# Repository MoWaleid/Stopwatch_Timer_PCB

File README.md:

# Programmable Logic Timer & Stopwatch (Digital Logic Design)

## Project Overview
A hardware-defined digital timing system engineered using **discrete logic ICs**. This project operates without a microcontroller, utilizing synchronous counters and combinational logic to provide high-precision **Stopwatch (Count-Up)** and **Timer (Countdown)** functionality. The system automates a **220V AC load** via a relay interface upon reaching a user-defined time target.

---

## Core Features
* **Dual Mode:** Stopwatch (00:00 to Target) and Timer (Start Time to 00:00).
* **MM:SS Display:** 4-digit 7-segment output.
* **Hardware Control:** Dedicated tactile buttons for **Set**, **Start/Pause**, and **Reset**.
* **Industrial Interfacing:** Relay module for 220V appliance automation.

---

## Technical Architecture
* **Time Base:** 1Hz pulse generation via a precision **555 Timer** circuit.
* **Logic Core:** Cascaded **74LS192** BCD up/down counters managed by logic gates for state transitions.
* **Display Driver:** **74LS47** BCD-to-7-segment decoders with multiplexing logic.
* **Trigger Logic:** Gate-level detection (AND/NOR) to activate the relay at the target time or zero.
* **Power Stage:** 5V DC logic isolated from the 220V AC output using a relay driver.

---

## Design & Implementation
1.  **Simulation:** Full functional validation in **Proteus** to verify synchronous timing and gate-level logic.
2.  **Schematic Capture:** Professional circuit design in **KiCad**.
3.  **PCB Layout:** Designed a production-ready PCB in **KiCad**, implementing specific trace widths for high-voltage safety and signal integrity.

---

## Components List
* **Counters:** 74LS192 BCD Counters.
* **Decoders:** 74LS47 BCD-to-7-Segment.
* **Logic Gates:** 74LS08 (AND), 74LS32 (OR), 74LS04 (NOT).
* **Timer:** NE555.
* **Output:** 5V Relay, LED.

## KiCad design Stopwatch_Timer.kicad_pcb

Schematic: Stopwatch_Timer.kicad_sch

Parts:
AFF1, AFF2, AFF3, AFF4: LTS-6960HR; 7SegmentLED_LTS6760_LTS6780
C1: 10u; C_Radial_D5.0mm_H11.0mm_P2.00mm
C2: 10n; C_Disc_D5.0mm_W2.5mm_P5.00mm
J3: Conn_01x06_Socket; PinSocket_1x06_P2.54mm_Vertical
MT1: 74LS192; DIP-16_W7.62mm_Socket
MU1: 74LS192; DIP-16_W7.62mm_Socket
R1: 1k; R_Axial_DIN0207_L6.3mm_D2.5mm_P7.62mm_Horizontal
R1_Timer1, R2_Timer1: 22k; R_Axial_DIN0207_L6.3mm_D2.5mm_P7.62mm_Horizontal
R3, R32, R33, R34, R35, R36, R37, R38, R40, R41, R42, R43, R44, R45, R46, R47: 330; R_Axial_DIN0207_L6.3mm_D2.5mm_P10.16mm_Horizontal
R3_Timer1, R4_Timer1, R5_Timer1, R6_Timer1, R50: 10k; R_Axial_DIN0207_L6.3mm_D2.5mm_P7.62mm_Horizontal
R4, R5, R6, R7, R8, R9, R10, R11, R12, R13, R14, R15, R16, R17, R18, R19, R20, R21, R22, R23, R24, R25, R26, R27, R28, R29, R30, R31, R39, R49: 330; R_Axial_DIN0207_L6.3mm_D2.5mm_P7.62mm_Horizontal
R_Mode1: 330; R_Axial_DIN0207_L6.3mm_D2.5mm_P7.62mm_Horizontal
S3, S4, S5: BUTT-2; SW_BUTT-2; PARTREV N/A
ST1: 74LS192; DIP-16_W7.62mm_Socket
SU1: 74LS192; DIP-16_W7.62mm_Socket
SW1, SW3: SW_DIP_x08; SW_DIP_SPSTx08_Slide_6.7x21.88mm_W7.62mm_P2.54mm_LowProfile
SW2: SW_DIP_x04; SW_DIP_SPSTx04_Slide_6.7x11.72mm_W7.62mm_P2.54mm_LowProfile
U1: NE555P; DIP-8_W7.62mm_Socket
U4, U6, U7, U9: 74LS47; DIP-16_W7.62mm_Socket
U10: 74LS157; DIP-16_W7.62mm_Socket
U11, U13: SN74HC04N; DIP-14_W7.62mm_Socket
U12, U21: CD4075BE; DIP-14_W7.62mm_Socket; DigiKey_Part_Number 296-2065-5-ND
U18, U20, U23: SN74HC32N; DIP-14_W7.62mm_Socket
U19, U24: SN74HC08N; DIP-14_W7.62mm_Socket
U22: CD4023BE; DIP-14_W7.62mm_Socket

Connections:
+5V: AFF1.3 (C.A.), AFF1.5 (DP), AFF1.8 (C.A.), AFF2.3 (C.A.), AFF2.5 (DP), AFF2.8 (C.A.), AFF3.3 (C.A.), AFF3.5 (DP), AFF3.8 (C.A.), AFF4.3 (C.A.), AFF4.5 (DP), AFF4.8 (C.A.), J3.1, J3.4, MT1.16 (VCC), MU1.16 (VCC), R1.2, R50.1, S4.1, S5.2, ST1.16 (VCC), SU1.16 (VCC), SW1.1, SW1.2, SW1.3, SW1.4, SW1.5, SW1.6, SW1.7, SW1.8, SW2.1, SW3.1, SW3.2, SW3.3, SW3.4, SW3.5, SW3.6, SW3.7, SW3.8, U1.4 (~RST), U1.8 (VCC), U4.3 (LT), U4.4 (BI), U4.5 (RBI), U4.16 (VCC), U6.3 (LT), U6.4 (BI), U6.5 (RBI), U6.16 (VCC), U7.3 (LT), U7.4 (BI), U7.5 (RBI), U7.16 (VCC), U9.3 (LT), U9.4 (BI), U9.5 (RBI), U9.16 (VCC), U10.3 (I1a), U10.10 (I1c), U10.16 (VCC), U11.14 (VCC), U12.14 (VDD), U13.14 (VCC), U18.14 (VCC), U19.14 (VCC), U20.14 (VCC), U21.14 (VDD), U22.8 (C), U22.14 (VDD), U24.14 (VCC)
GND: C1.2, C2.2, J3.2, J3.6, MT1.8 (GND), MU1.8 (GND), R3.2, R32.2, R33.2, R34.2, R35.2, R36.2, R37.2, R38.2, R40.2, R41.2, R42.2, R43.2, R44.2, R45.2, R46.2, R47.2, R49.2, R_Mode1.2, S3.1, ST1.8 (GND), SU1.8 (GND), U1.1 (GND), U4.8 (GND), U6.8 (GND), U7.8 (GND), U9.8 (GND), U10.6 (I1b), U10.8 (GND), U10.13 (I1d), U10.15 (E), U11.7 (GND), U12.7 (VSS), U13.7 (GND), U18.7 (GND), U19.7 (GND), U20.7 (GND), U21.7 (VSS), U22.7 (VSS), U23.7 (GND), U24.7 (GND), U24.12 (4A), U24.13 (4B)
unnamed: AFF1.7 (a), R4.2
unnamed: AFF1.6 (b), R5.2
unnamed: AFF1.4 (c), R6.2
unnamed: AFF1.2 (d), R7.2
unnamed: AFF1.1 (e), R8.2
unnamed: AFF1.9 (f), R9.2
unnamed: AFF1.10 (g), R10.2
unnamed: AFF2.7 (a), R11.2
unnamed: AFF2.6 (b), R12.2
unnamed: AFF2.4 (c), R13.2
unnamed: AFF2.2 (d), R14.2
unnamed: AFF2.1 (e), R15.2
unnamed: AFF2.9 (f), R16.2
unnamed: AFF2.10 (g), R17.2
unnamed: AFF3.7 (a), R18.2
unnamed: AFF3.6 (b), R19.2
unnamed: AFF3.4 (c), R20.2
unnamed: AFF3.2 (d), R21.2
unnamed: AFF3.1 (e), R22.2
unnamed: AFF3.9 (f), R23.2
unnamed: AFF3.10 (g), R24.2
unnamed: AFF4.7 (a), R25.2
unnamed: AFF4.6 (b), R26.2
unnamed: AFF4.4 (c), R27.2
unnamed: AFF4.2 (d), R28.2
unnamed: AFF4.1 (e), R29.2
unnamed: AFF4.9 (f), R30.2
unnamed: AFF4.10 (g), R31.2
unnamed: J3.5, U13.13 (6A), U18.8 (3Y)
unnamed: MT1.15 (A), R43.1, SW3.13
unnamed: MT1.1 (B), R42.1, SW3.14
unnamed: MT1.10 (C), R41.1, SW3.15
unnamed: MT1.14 (CLR), MU1.14 (CLR), SU1.14 (CLR), U20.8 (3Y), U23.2 (1B)
unnamed: MT1.9 (D), R40.1, SW3.16
unnamed: MT1.4 (DOWN), MU1.13 (~BO)
unnamed: MT1.3 (QA), U6.7 (A), U21.1 (A)
unnamed: MT1.2 (QB), U6.1 (B), U21.2 (B)
unnamed: MT1.6 (QC), U6.2 (C), U21.8 (C)
unnamed: MT1.7 (QD), U6.6 (D), U21.3 (D)
unnamed: MT1.5 (UP), MU1.12 (~CO)
unnamed: MT1.11 (~LOAD), MU1.11 (~LOAD), R50.2, S3.2, SU1.11 (~LOAD), U19.1 (1A), U24.1 (1A)
unnamed: MU1.15 (A), R47.1, SW3.9
unnamed: MU1.1 (B), R46.1, SW3.10
unnamed: MU1.10 (C), R45.1, SW3.11
unnamed: MU1.9 (D), R44.1, SW3.12
unnamed: MU1.4 (DOWN), ST1.13 (~BO)
unnamed: MU1.3 (QA), U4.7 (A), U21.4 (E)
unnamed: MU1.2 (QB), U4.1 (B), U21.5 (F)
unnamed: MU1.6 (QC), U4.2 (C), U21.13 (G)
unnamed: MU1.7 (QD), U4.6 (D), U21.12 (H)
unnamed: MU1.5 (UP), U11.4 (2Y)
unnamed: R1_Timer1.2, R2_Timer1.1
unnamed: R2_Timer1.2, R3_Timer1.1
unnamed: R3_Timer1.2, R4_Timer1.1
unnamed: R4_Timer1.2, R5_Timer1.1
unnamed: R5_Timer1.2, R6_Timer1.1
unnamed: ST1.15 (A), U10.4 (Za)
unnamed: ST1.1 (B), U10.7 (Zb)
unnamed: ST1.10 (C), U10.9 (Zc)
unnamed: ST1.14 (CLR), U23.3 (1Y)
unnamed: ST1.9 (D), U10.12 (Zd)
unnamed: ST1.4 (DOWN), SU1.13 (~BO)
unnamed: ST1.3 (QA), U7.7 (A), U21.11 (I), U22.1 (A)
unnamed: ST1.2 (QB), U7.1 (B), U12.1 (A), U24.9 (3A)
unnamed: ST1.6 (QC), U7.2 (C), U12.2 (B), U24.10 (3B)
unnamed: ST1.7 (QD), U7.6 (D), U12.8 (C), U22.2 (B)
unnamed: ST1.5 (UP), SU1.12 (~CO)
unnamed: ST1.11 (~LOAD), U24.3 (1Y)
unnamed: R38.1, SU1.15 (A), SW1.9
unnamed: R37.1, SU1.1 (B), SW1.10
unnamed: R36.1, SU1.10 (C), SW1.11
unnamed: R35.1, SU1.9 (D), SW1.12
unnamed: SU1.4 (DOWN), U20.6 (2Y)
unnamed: SU1.3 (QA), U9.7 (A), U12.3 (D)
unnamed: SU1.2 (QB), U9.1 (B), U12.4 (E)
unnamed: SU1.6 (QC), U9.2 (C), U12.5 (F)
unnamed: SU1.7 (QD), U9.6 (D), U12.13 (G)
unnamed: SU1.5 (UP), U20.3 (1Y)
unnamed: C2.1, U1.5 (CONT)
unnamed: R1.1, R1_Timer1.1, U1.7 (DISCH)
unnamed: R39.1, U1.3 (OUT)
unnamed: C1.1, R6_Timer1.2, U1.2 (TRIG), U1.6 (THRES)
unnamed: R11.1, U4.13 (a)
unnamed: R12.1, U4.12 (b)
unnamed: R13.1, U4.11 (c)
unnamed: R14.1, U4.10 (d)
unnamed: R15.1, U4.9 (e)
unnamed: R16.1, U4.15 (f)
unnamed: R17.1, U4.14 (g)
unnamed: R4.1, U6.13 (a)
unnamed: R5.1, U6.12 (b)
unnamed: R6.1, U6.11 (c)
unnamed: R7.1, U6.10 (d)
unnamed: R8.1, U6.9 (e)
unnamed: R9.1, U6.15 (f)
unnamed: R10.1, U6.14 (g)
unnamed: R18.1, U7.13 (a)
unnamed: R19.1, U7.12 (b)
unnamed: R20.1, U7.11 (c)
unnamed: R21.1, U7.10 (d)
unnamed: R22.1, U7.9 (e)
unnamed: R23.1, U7.15 (f)
unnamed: R24.1, U7.14 (g)
unnamed: R25.1, U9.13 (a)
unnamed: R26.1, U9.12 (b)
unnamed: R27.1, U9.11 (c)
unnamed: R28.1, U9.10 (d)
unnamed: R29.1, U9.9 (e)
unnamed: R30.1, U9.15 (f)
unnamed: R31.1, U9.14 (g)
unnamed: R34.1, SW1.13, U10.2 (I0a)
unnamed: R33.1, SW1.14, U10.5 (I0b)
unnamed: R32.1, SW1.15, U10.11 (I0c)
unnamed: R3.1, SW1.16, U10.14 (I0d)
unnamed: U10.1 (S), U11.2 (1Y)
unnamed: U11.1 (1A), U22.9 (J*~(A.B.C)), U24.2 (1B)
unnamed: U11.3 (2A), U23.1 (1A), U24.6 (2Y)
unnamed: R_Mode1.1, SW2.8, U11.5 (3A), U13.1 (1A), U19.5 (2B), U20.2 (1B)
unnamed: U11.6 (3Y), U24.4 (2A)
unnamed: U12.9 (J*A+B+C), U12.12 (H)
unnamed: U12.6 (K*D+E+F), U12.11 (I)
unnamed: U12.10 (L*G+H+I), U18.5 (2B)
unnamed: U13.2 (1Y), U20.5 (2B)
unnamed: U13.12 (6Y), U19.2 (1B)
unnamed: U18.1 (1A), U21.9 (J*A+B+C)
unnamed: U18.2 (1B), U21.6 (K*D+E+F)
unnamed: U18.3 (1Y), U18.9 (3A)
unnamed: U18.4 (2A), U21.10 (L*G+H+I)
unnamed: U18.6 (2Y), U18.10 (3B)
unnamed: U19.3 (1Y), U19.4 (2A)
unnamed: U19.6 (2Y), U20.10 (3B)
unnamed: R39.2, S5.1, U20.1 (1A), U20.4 (2A)
unnamed: R49.1, S4.2, U20.9 (3A)
unnamed: U24.5 (2B), U24.8 (3Y)

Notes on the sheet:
Not Gate
Big Or Output
Count Up/Down
NAND Gate
LSB
Output for MR
Output of triple And
Up Or
Set Button
Clock
Not of Count/Up Down
Or Output
Mux
Big And Output
NAND OF MSB and LSB
Count Up/DOwn
Middle Bits
Down Or
MSB
Not of Big Or Output
Not of NAND
Not of Count Up/Down
Start/Pause
Not Of Big Or
Output of triple AND
555 Timer
Output of Middle Bits
Set Button
Not output of triple AND
2-Input AND
PL input of second counter
Their Output
AND
Global Reset
Count UP/Down
Or Gate

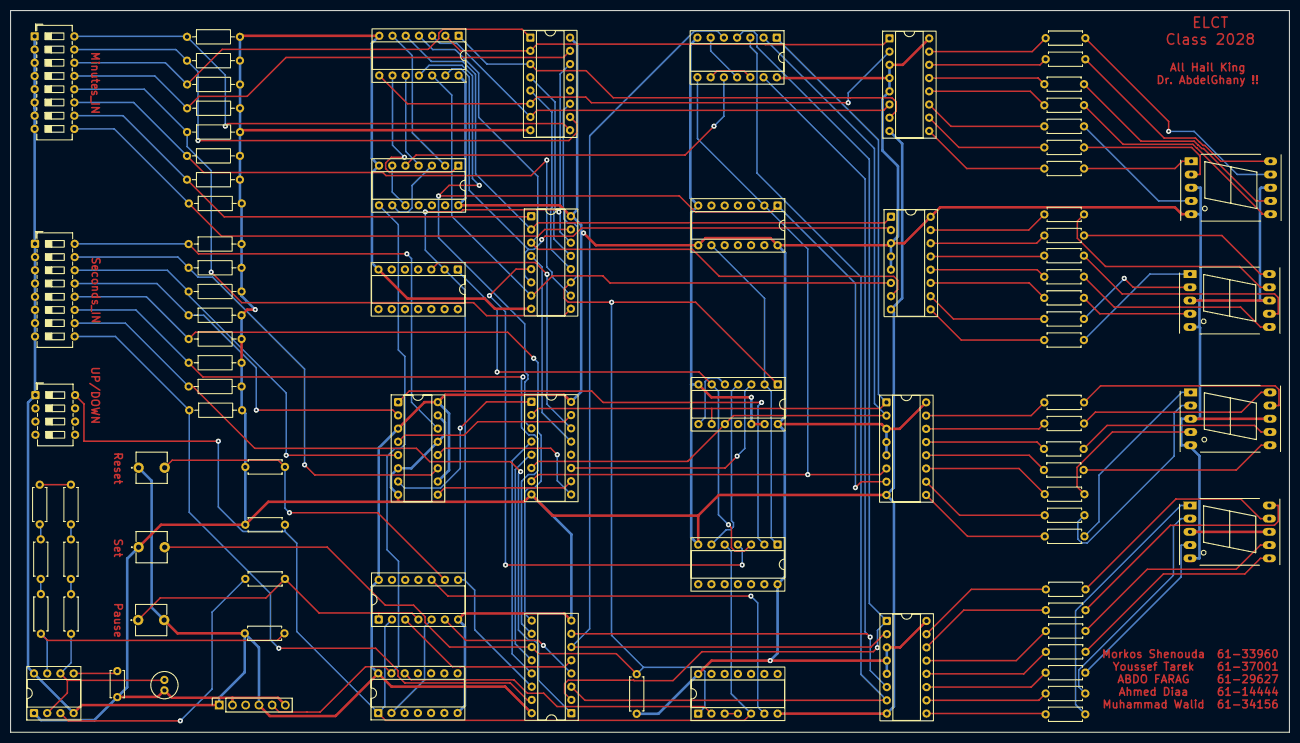
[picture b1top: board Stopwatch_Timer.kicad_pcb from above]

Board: 2 copper layers, 245.6 x 138.6 mm, 88 parts (0 on the bottom side), 136 nets.

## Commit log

2026-02-28 initiated the project
2026-02-28 Testing the CADLAB
2026-02-28 Second Test
2026-02-28 Test parallel work
2026-02-28 Backlink to CADLAB.io has been added.
2026-03-01 Done part of the routing
2026-03-02 Final PCB design
2026-03-03 Finalized PCB design
2026-03-05 replaced silkscreen text with copper text
2026-03-11 Proteus simulation file
2026-03-11 Add README for Programmable Logic Timer & Stopwatch
    Added detailed project overview, core features, technical architecture, design and implementation steps, and components list for the Programmable Logic Timer & Stopwatch.
2026-03-13 Refine wording in README for clarity
    Removed redundant wording for clarity in features and implementation sections.
